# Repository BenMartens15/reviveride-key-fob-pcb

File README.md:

# ReviveRide: Modernizing Vintage Autos
### Project Overview
ReviveRide was developed as a capstone project for the Computer Engineering Technology program at Conestoga College. The goal of ReviveRide is to bring features found on modern vehicles to older vehicles. The project provides a dash camera, backup camera, head unit touchscreen with Android Auto, blind spot object detection, and remote start in an all-in-one, easy to install kit.

### Key Fob
The key fob wirelessly sends a signal to the control module telling it to start the car.

This repo contains the schematic and PCB for the key fob. The firmware for the key fob can be found here: https://github.com/BenMartens15/reviveride-key-fob-firmware

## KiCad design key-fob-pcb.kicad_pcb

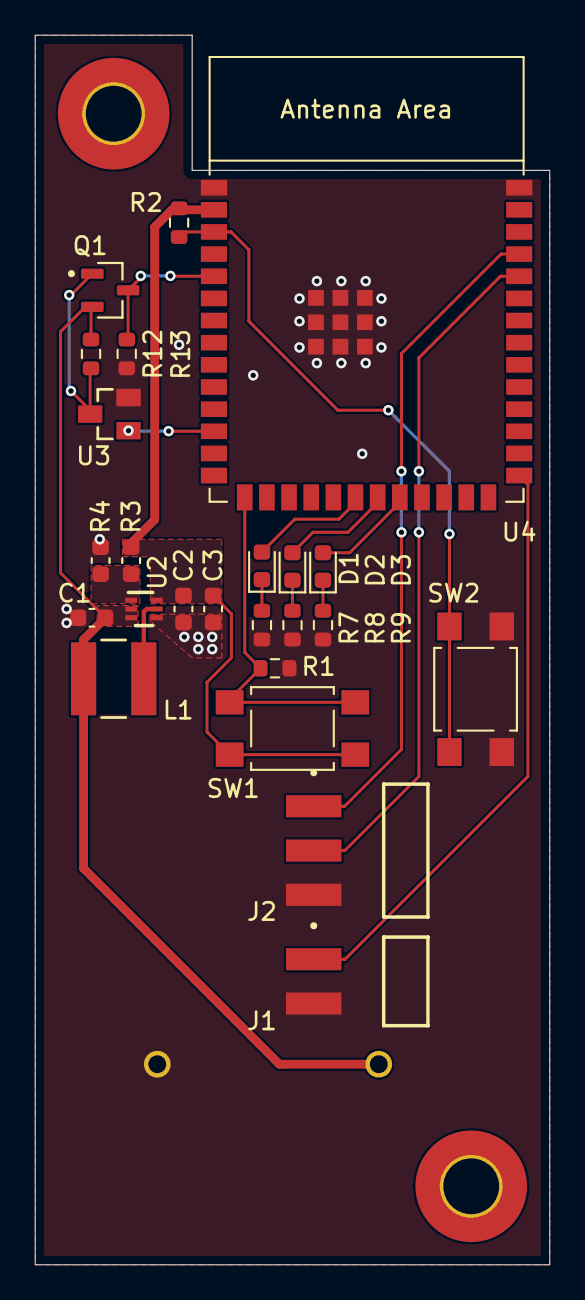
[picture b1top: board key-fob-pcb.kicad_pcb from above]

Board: 2 copper layers, 29.5 x 70.5 mm, 25 parts (1 on the bottom side), 19 nets.

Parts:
BT1: 2468; BAT_2468
C1: 10u; C_0603_1608Metric
C2, C3: 22u; C_0603_1608Metric
D1: LED1; LED_0603_1608Metric
D2: LED2; LED_0603_1608Metric
D3: LED3; LED_0603_1608Metric
J1: Programming Jumper; SAMTEC_TSM-102-01-L-SH
J2: Programming Header; SAMTEC_TSM-103-01-L-SH-TR
L1: 74404043010A; IND_43010A_WRE
Q1: IRLML6402TRPBF; SOT95P237X112-3N
R1, R2: 10k; R_0603_1608Metric
R3: 453k; C_0603_1608Metric
R4: 100k; C_0603_1608Metric
R7, R8, R9: 220; R_0603_1608Metric
R12, R13: 100k; R_0603_1608Metric
SW1: START/STOP BTN; SW_SPST_TL3305B
SW2: EN; SW_SPST_TL3305B
U2: TPS61023DRLT; DRL0006A
U3: IRLML2502TRPBF; SOT23
U4: ESP32-S3-WROOM-1

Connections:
/ADC/VIN: BT1.P, C1.1, L1.2, Q1.2, R12.1, U2.2 (EN), U2.3 (VIN)
/BOOT: J1.1, U4.27 (GPIO0/BOOT)
/EN: R2.2, SW2.2, U4.3 (EN)
/ESP32/VCC: C2.1, C3.1, R2.1, R3.1, SW1.1, U2.6 (VOUT), U4.2 (3V3)
/LED1: D1.2 (A), U4.20 (GPIO12/TOUCH12/ADC2_CH1/FSPICLK/FSPIIO6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)
/LED2: D2.2 (A), U4.21 (GPIO13/TOUCH13/ADC2_CH2/FSPIQ/FSPIIO7/S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)
/LED3: D3.2 (A), U4.22 (GPIO14/TOUCH14/ADC2_CH3/FSPIWP/FSPIDQS/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)
/RX: J2.2, U4.36 (U0RXD/GPIO44/CLK_OUT2)
/START_STOP: R1.2, SW1.2, U4.15 (GPIO3/TOUCH3/ADC1_CH2)
/TX: J2.1, U4.37 (U0TXD/GPIO43/CLK_OUT1)
/VBAT_ADC: Q1.3, R13.1, U4.5 (GPIO5/TOUCH5/ADC1_CH4)
/VBAT_ADC_EN: U3.1, U4.12 (GPIO8/TOUCH8/ADC1_CH7/SUBSPICS1)
GND: BT1.N, C1.2, C2.2, C3.2, J1.2, J2.3, R1.1, R4.2, R7.1, R8.1, R9.1, R13.2, SW2.1, U2.4 (GND), U3.2, U4.1 (GND), U4.40 (GND), U4.41 (GND)
unnamed: D1.1 (K), R7.2
unnamed: D2.1 (K), R8.2
unnamed: D3.1 (K), R9.2
unnamed: Q1.1, R12.2, U3.3
unnamed: R3.2, R4.1, U2.1 (FB)
unnamed: L1.1, U2.5 (SW)

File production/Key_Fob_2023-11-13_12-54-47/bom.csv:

Designator,Footprint,Quantity,Value,LCSC Part #
C1,0402,1,10u,C3009906
C2,0402,1,4.7u,
D1,0603,1,LED1,C128249
D2,0603,1,LED2,C2986018
L1,IND_43010A_WRE,1,74404043010A,
Q1,SOT95P237X112-3N,1,IRLML6402TRPBF,C2593
R1,0603,1,10k,C2924175
"R12, R13",0603,2,100k,C5369222
R3,0402,1,453k,C843903
R4,0402,1,100k,C844712
"R7, R8",0603,2,220,C844757
U1,ESP32-S3-MINI-1,1,ESP32-S3-MINI-1,C2913206
U2,DRL0006A,1,TPS61023DRLT,C919459
U3,SOT23,1,IRLML2502TRPBF,C2589

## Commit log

2023-10-18 basic schematic complete
2023-10-19 changed button to active high and added a few DNP buttons
2023-11-01 add ADC circuit, a few more DNP components, and assigned footprints
2023-11-02 create libraries folder for sharing external libs
2023-11-06 inital layout of components complete
2023-11-08 layout complete
2023-11-13 generate fab files
2023-11-13 minor changes
2023-11-23 replace GND heriarchical labels with GND symbols
2023-11-23 add author to each sheet
2024-01-12 add BOM files to git
2024-02-09 add 3D models and generate STEP file for PCB
2024-02-09 switched to full-sized ESP32 S3 WROOM and redid PCB layout
2024-02-09 generate gerbers
2024-02-19 update 3D models and generate PCB step file
